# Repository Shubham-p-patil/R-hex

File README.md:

# R-hex
Negotiating difficult terrains has always been a challenging task for wheeled robots. To solve this issue, man has been trying to design various legged robots, taking inspiration from nature. Out of all these legged robots, six legged robots are the most common ones, since 6 legs have an edge over other legged robots considering their stability. In hexapods, generally a tripod gait is in used in which 2 sets of legs(3 each ) are alternatively on the ground. This hexapod is our attempt to tackle the same issue of all terrain driving capabilities. Instead of normal legs we have used C-shaped legs which have an added advantage of climbing obstacles, pretty taller than itself.

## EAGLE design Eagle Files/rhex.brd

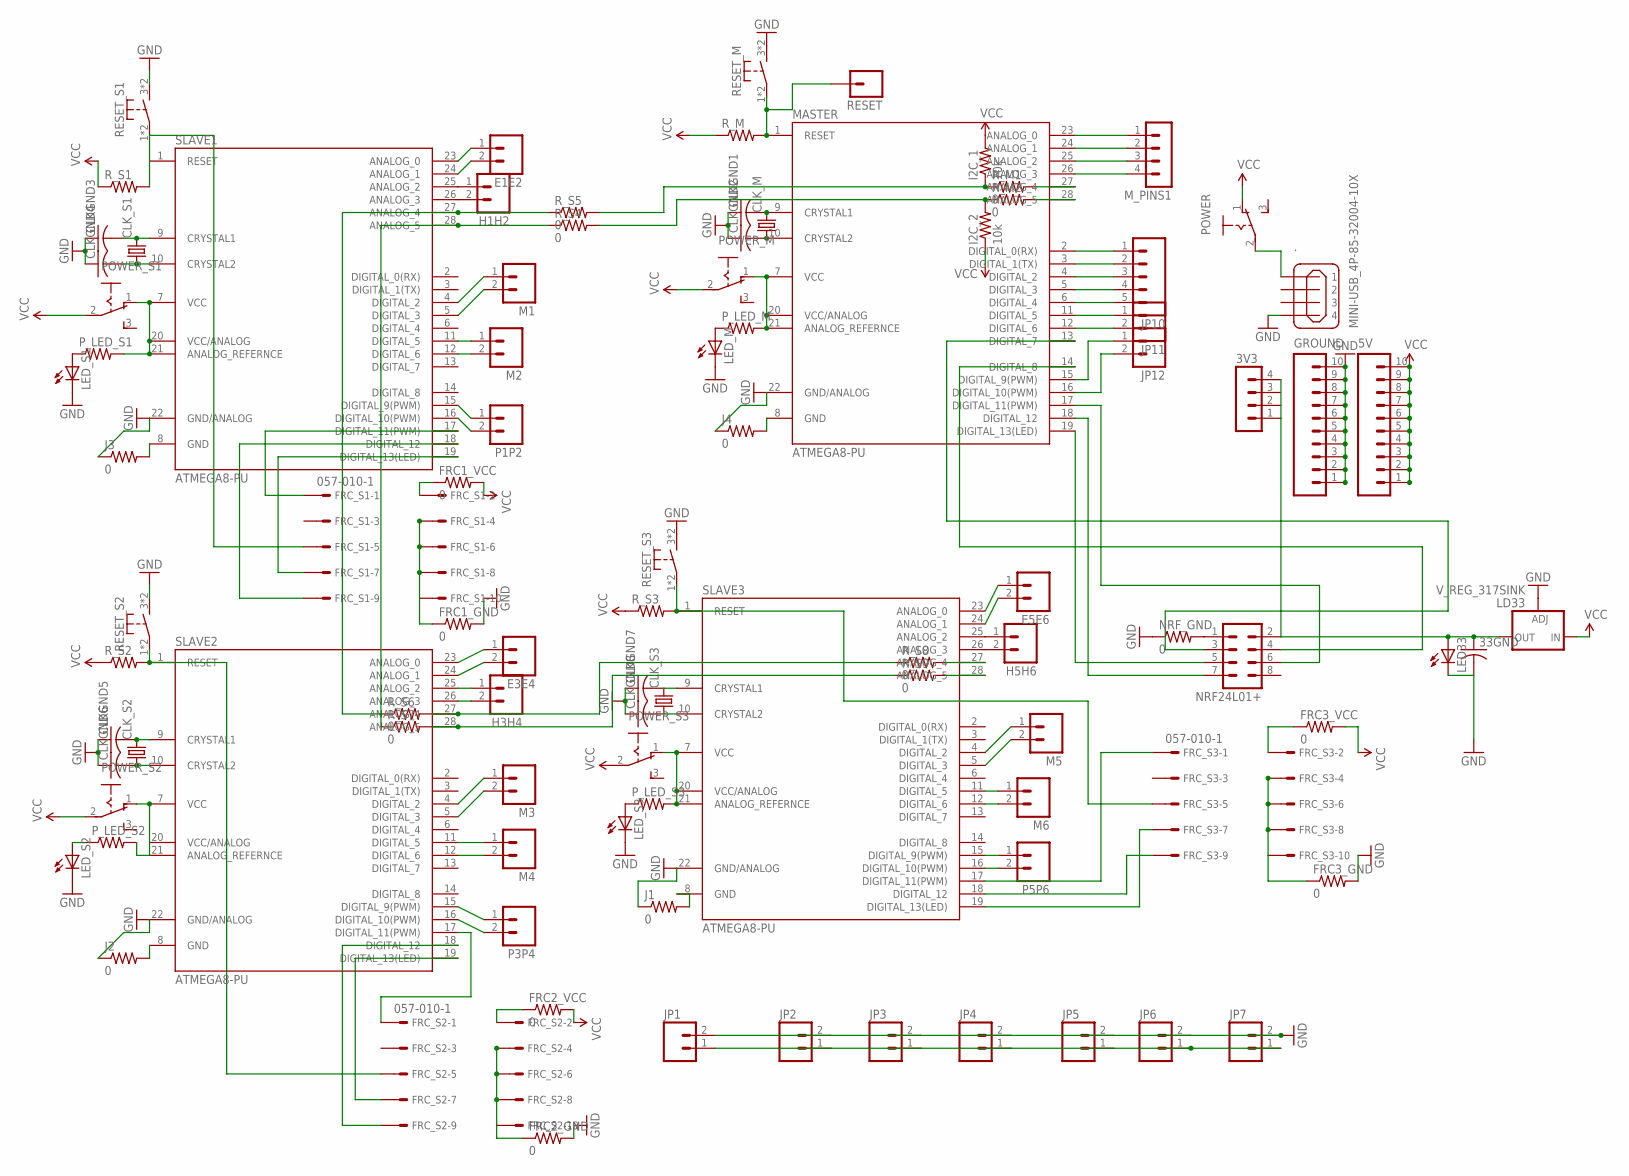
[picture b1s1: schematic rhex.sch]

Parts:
3V3: MA04-1
5V: M10SILK_FEMALE_PTH; 1X10
33GND: C-US050-024X044; C050-024X044
.: MINI-USB_4P-85-32004-10X; 85-32004-10X
CLKGND1, CLKGND2, CLKGND3, CLKGND4, CLKGND5, CLKGND6, CLKGND7, CLKGND8: C-US050-024X044; C050-024X044
CLK_M: CRYSTALHC49U-V; HC49U-V
CLK_S1, CLK_S2, CLK_S3: CRYSTALHC49U-V; HC49U-V
E1E2, E3E4, E5E6: M02LOCK; 1X02_LOCK
FRC1_GND, FRC1_VCC, FRC2_GND, FRC2_VCC, FRC3_GND, FRC3_VCC: 0; 0411/15
FRC_S1, FRC_S2, FRC_S3: 057-010-1
GROUND: M10SILK_FEMALE_PTH; 1X10
H1H2, H3H4, H5H6: M02LOCK; 1X02_LOCK
I2C_1, I2C_2: 10k; 0411/15
J1, J2, J3, J4: 0; 0411/15
JP1, JP2, JP3, JP4, JP5, JP6, JP7: M023.5MM; SCREWTERMINAL-3.5MM-2
JP10: M05PTH; 1X05
JP11, JP12: M02PTH; 1X02
LD33: V_REG_317SINK; TO220-ADJ
LED33: LED3MM
LED_M: LED3MM
LED_S1, LED_S2, LED_S3: LED3MM
M1, M2, M3, M4, M5, M6: M02LOCK; 1X02_LOCK
MASTER: ATMEGA8-PU; DIL28-3
M_PINS1: MA04-1
NRF24L01+: MA04-2
NRF_GND: 0; 0411/15
P1P2, P3P4, P5P6: M02LOCK; 1X02_LOCK
POWER: M251
POWER_M: M251
POWER_S1, POWER_S2, POWER_S3: M251
P_LED_M: R-US_0411/15; 0411/15
P_LED_S1, P_LED_S2, P_LED_S3: R-US_0411/15; 0411/15
RESET: M01PTH; 1X01
RESET_M: SW-TACTILE-6X6; SW6X6
RESET_S1, RESET_S2, RESET_S3: SW-TACTILE-6X6; SW6X6
R_M: R-US_0411/15; 0411/15
R_M1, R_M2: 0; 0411/15
R_S1, R_S2, R_S3: R-US_0411/15; 0411/15
R_S4, R_S5, R_S6, R_S7, R_S8, R_S9: 0; 0411/15
SLAVE1, SLAVE2, SLAVE3: ATMEGA8-PU; DIL28-3

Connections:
3V3: 3V3.1, 3V3.4, 33GND.1, LD33.OUT, LED33.A, NRF24L01+.2
12V: JP1.1, JP2.1, JP3.1, JP4.1, JP5.1, JP6.1, JP7.1
GND: 33GND.2, ..4, CLKGND1.1, CLKGND2.1, CLKGND3.1, CLKGND4.1, CLKGND5.1, CLKGND6.1, CLKGND7.1, CLKGND8.1, FRC1_GND.2, FRC2_GND.2, FRC3_GND.2, GROUND.1, GROUND.2, GROUND.3, GROUND.4, GROUND.5, GROUND.6, GROUND.7, GROUND.8, GROUND.9, GROUND.10, J1.1, J2.1, J3.1, J4.1, JP1.2, JP2.2, JP3.2, JP4.2, JP5.2, JP6.2, JP7.2, LD33.ADJ, LED33.K (C), LED_M.K (C), LED_S1.K (C), LED_S2.K (C), LED_S3.K (C), MASTER.22 (GND/ANALOG), NRF_GND.1, RESET_M.3 (S1), RESET_M.4 (S1), RESET_S1.3 (S1), RESET_S1.4 (S1), RESET_S2.3 (S1), RESET_S2.4 (S1), RESET_S3.3 (S1), RESET_S3.4 (S1), SLAVE1.22 (GND/ANALOG), SLAVE2.22 (GND/ANALOG), SLAVE3.22 (GND/ANALOG)
unnamed: CLKGND1.2, CLK_M.2, MASTER.9 (CRYSTAL1)
unnamed: CLKGND2.2, CLK_M.1, MASTER.10 (CRYSTAL2)
unnamed: MASTER.1 (RESET), RESET.1, RESET_M.1, RESET_M.2 (P1), R_M.2
unnamed: FRC_S2.1, SLAVE2.17 (DIGITAL_11(PWM))
unnamed: FRC_S3.5, RESET_S3.1, RESET_S3.2 (P1), R_S3.2, SLAVE3.1 (RESET)
unnamed: FRC_S2.5, RESET_S2.1, RESET_S2.2 (P1), R_S2.2, SLAVE2.1 (RESET)
unnamed: M3.1, SLAVE2.4 (DIGITAL_2)
unnamed: MASTER.19 (DIGITAL_13(LED)), NRF24L01+.5
unnamed: MASTER.18 (DIGITAL_12), NRF24L01+.7
unnamed: MASTER.17 (DIGITAL_11(PWM)), NRF24L01+.6
unnamed: R_S5.1, R_S6.1, SLAVE1.27 (ANALOG_4)
unnamed: R_S4.1, R_S7.1, SLAVE1.28 (ANALOG_5)
unnamed: M1.1, SLAVE1.4 (DIGITAL_2)
unnamed: M1.2, SLAVE1.5 (DIGITAL_3)
unnamed: M3.2, SLAVE2.5 (DIGITAL_3)
unnamed: M5.1, SLAVE3.4 (DIGITAL_2)
unnamed: M2.1, SLAVE1.11 (DIGITAL_5)
unnamed: MASTER.13 (DIGITAL_7), NRF24L01+.3
unnamed: M5.2, SLAVE3.5 (DIGITAL_3)
unnamed: M4.1, SLAVE2.11 (DIGITAL_5)
unnamed: M4.2, SLAVE2.12 (DIGITAL_6)
unnamed: M6.1, SLAVE3.11 (DIGITAL_5)
unnamed: M6.2, SLAVE3.12 (DIGITAL_6)
unnamed: M2.2, SLAVE1.12 (DIGITAL_6)
unnamed: JP10.1, MASTER.2 (DIGITAL_0(RX))
unnamed: I2C_2.2, R_M2.1, R_S4.2
unnamed: NRF24L01+.1, NRF_GND.2
unnamed: FRC_S2.7, SLAVE2.19 (DIGITAL_13(LED))
unnamed: E1E2.1, SLAVE1.23 (ANALOG_0)
unnamed: E1E2.2, SLAVE1.24 (ANALOG_1)
unnamed: E3E4.1, SLAVE2.23 (ANALOG_0)
unnamed: E3E4.2, SLAVE2.24 (ANALOG_1)
unnamed: E5E6.1, SLAVE3.23 (ANALOG_0)
unnamed: E5E6.2, SLAVE3.24 (ANALOG_1)
unnamed: CLKGND3.2, CLK_S1.2, SLAVE1.9 (CRYSTAL1)
unnamed: CLKGND4.2, CLK_S1.1, SLAVE1.10 (CRYSTAL2)
unnamed: CLKGND5.2, CLK_S2.2, SLAVE2.9 (CRYSTAL1)
unnamed: P3P4.1, SLAVE2.15 (DIGITAL_9(PWM))
unnamed: P3P4.2, SLAVE2.16 (DIGITAL_10(PWM))
unnamed: CLKGND6.2, CLK_S2.1, SLAVE2.10 (CRYSTAL2)
unnamed: CLKGND7.2, CLK_S3.2, SLAVE3.9 (CRYSTAL1)
unnamed: CLKGND8.2, CLK_S3.1, SLAVE3.10 (CRYSTAL2)
unnamed: FRC_S2.9, SLAVE2.18 (DIGITAL_12)
unnamed: ..1, POWER.2
unnamed: FRC_S3.1, SLAVE3.17 (DIGITAL_11(PWM))
unnamed: POWER_S1.1 (O), P_LED_S1.2, SLAVE1.7 (VCC), SLAVE1.20 (VCC/ANALOG), SLAVE1.21 (ANALOG_REFERNCE)
unnamed: FRC_S3.7, SLAVE3.19 (DIGITAL_13(LED))
unnamed: FRC_S3.9, SLAVE3.18 (DIGITAL_12)
unnamed: FRC_S1.7, SLAVE1.19 (DIGITAL_13(LED))
unnamed: FRC_S1.9, SLAVE1.18 (DIGITAL_12)
unnamed: FRC_S1.1, SLAVE1.17 (DIGITAL_11(PWM))
unnamed: P1P2.1, SLAVE1.15 (DIGITAL_9(PWM))
unnamed: POWER_S2.1 (O), P_LED_S2.2, SLAVE2.7 (VCC), SLAVE2.20 (VCC/ANALOG), SLAVE2.21 (ANALOG_REFERNCE)
unnamed: MASTER.7 (VCC), MASTER.20 (VCC/ANALOG), MASTER.21 (ANALOG_REFERNCE), POWER_M.1 (O), P_LED_M.2
unnamed: POWER_S3.1 (O), P_LED_S3.2, SLAVE3.7 (VCC), SLAVE3.20 (VCC/ANALOG), SLAVE3.21 (ANALOG_REFERNCE)
unnamed: P1P2.2, SLAVE1.16 (DIGITAL_10(PWM))
unnamed: P5P6.1, SLAVE3.15 (DIGITAL_9(PWM))
unnamed: P5P6.2, SLAVE3.16 (DIGITAL_10(PWM))
unnamed: H5H6.1, SLAVE3.25 (ANALOG_2)
unnamed: H5H6.2, SLAVE3.26 (ANALOG_3)
unnamed: H1H2.1, SLAVE1.25 (ANALOG_2)
unnamed: H1H2.2, SLAVE1.26 (ANALOG_3)
unnamed: H3H4.1, SLAVE2.25 (ANALOG_2)
unnamed: H3H4.2, SLAVE2.26 (ANALOG_3)
unnamed: LED_S1.A, P_LED_S1.1
unnamed: LED_M.A, P_LED_M.1
unnamed: LED_S3.A, P_LED_S3.1
unnamed: FRC2_GND.1, FRC_S2.4, FRC_S2.6, FRC_S2.8, FRC_S2.10
unnamed: LED_S2.A, P_LED_S2.1
unnamed: JP10.2, MASTER.3 (DIGITAL_1(TX))
unnamed: JP10.3, MASTER.4 (DIGITAL_2)
unnamed: JP10.4, MASTER.5 (DIGITAL_3)
unnamed: JP10.5, MASTER.6 (DIGITAL_4)
unnamed: JP11.1, MASTER.11 (DIGITAL_5)
unnamed: JP11.2, MASTER.12 (DIGITAL_6)
unnamed: JP12.1, MASTER.15 (DIGITAL_9(PWM))
unnamed: JP12.2, MASTER.16 (DIGITAL_10(PWM))
unnamed: MASTER.14 (DIGITAL_8), NRF24L01+.4
unnamed: MASTER.23 (ANALOG_0), M_PINS1.1
unnamed: MASTER.24 (ANALOG_1), M_PINS1.2
unnamed: MASTER.25 (ANALOG_2), M_PINS1.3
unnamed: MASTER.26 (ANALOG_3), M_PINS1.4
unnamed: J1.2, SLAVE3.8 (GND)
unnamed: J2.2, SLAVE2.8 (GND)
unnamed: J3.2, SLAVE1.8 (GND)
unnamed: J4.2, MASTER.8 (GND)
unnamed: FRC1_GND.1, FRC_S1.4, FRC_S1.6, FRC_S1.8, FRC_S1.10
unnamed: FRC_S1.5, RESET_S1.1, RESET_S1.2 (P1), R_S1.2, SLAVE1.1 (RESET)
unnamed: FRC3_GND.1, FRC_S3.4, FRC_S3.6, FRC_S3.8, FRC_S3.10
unnamed: FRC1_VCC.1, FRC_S1.2
unnamed: FRC2_VCC.1, FRC_S2.2
unnamed: FRC3_VCC.1, FRC_S3.2
unnamed: I2C_1.1, R_M1.1, R_S5.2
unnamed: R_S6.2, R_S8.1, SLAVE2.27 (ANALOG_4)
unnamed: R_S7.2, R_S9.1, SLAVE2.28 (ANALOG_5)
unnamed: R_S8.2, SLAVE3.27 (ANALOG_4)
unnamed: R_S9.2, SLAVE3.28 (ANALOG_5)
unnamed: MASTER.27 (ANALOG_4), R_M1.2
unnamed: MASTER.28 (ANALOG_5), R_M2.2
VCC: 5V.1, 5V.2, 5V.3, 5V.4, 5V.5, 5V.6, 5V.7, 5V.8, 5V.9, 5V.10, FRC1_VCC.2, FRC2_VCC.2, FRC3_VCC.2, I2C_1.2, I2C_2.1, LD33.IN, POWER.1 (O), POWER_M.2, POWER_S1.2, POWER_S2.2, POWER_S3.2, R_M.1, R_S1.1, R_S2.1, R_S3.1

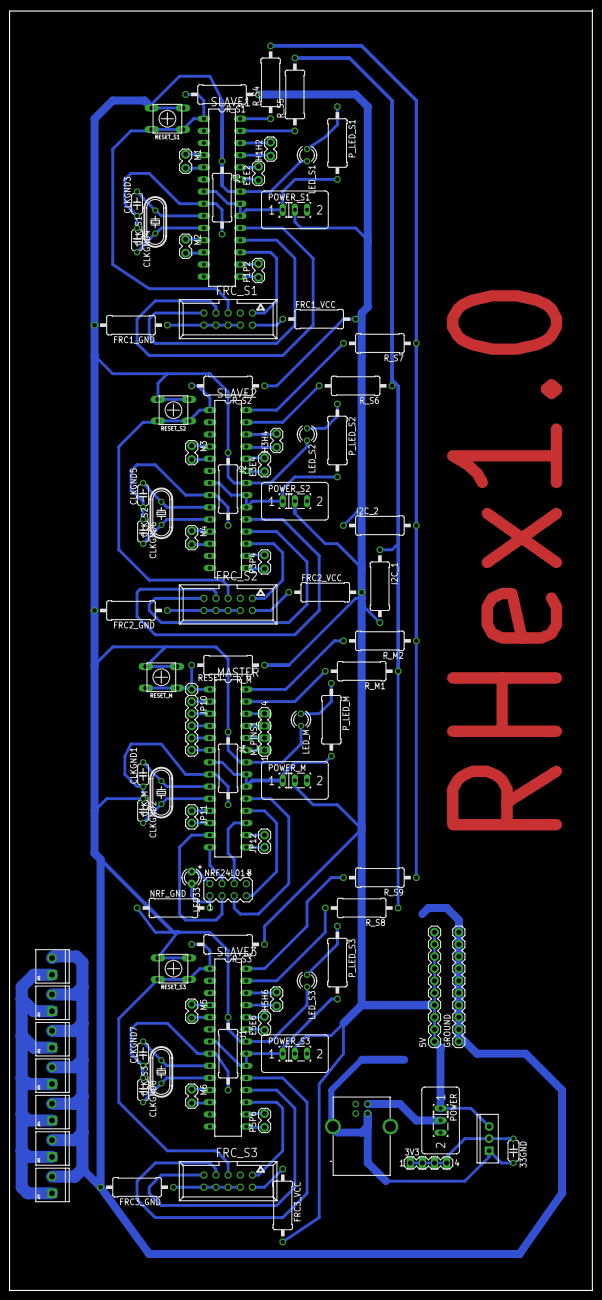
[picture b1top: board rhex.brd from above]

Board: 2 copper layers, 121.9 x 267.9 mm, 96 parts (0 on the bottom side), 103 nets.

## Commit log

2018-01-11 Final

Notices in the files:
parts and their libraries:
SparkFun-Connectors: Licensing: Creative Commons ShareAlike 4.0 International - https://creativecommons.org/licenses/by-sa/4.0
